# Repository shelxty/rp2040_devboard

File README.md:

# RP2040 Devboard

This is a compact, breakout-friendly devboard (2-layer PCB) built around the Raspberry Pi 2040 microcontroller. It contains an onboard QSPI flash, USB-C, and 30 GPIO pins broken out to dual 20-pin headers. 

It's designed as a base for embedded projects, with every usable GPIO routed to a header pin to be used on a breadboard or custom carrier PCB. 

## Components 

| Reference | Part | Description | Package | 
| ---------- | ----- | ---------- | --------- | 
| U1 | RP2040 | Dual-core MCU | QFN-56, 7x7 mm | 
| U2 | MCPI1700-3.3 | 3.3V LDO regulator | SOT-89-3 | 
| U3 | W25Q128JVS | 16 MB QSPI flash | USON-3, 3x2 mm | 
| Y1 | Crystal | 12 MHz (GND24 style) | 3.2x2.5 mm SMD | 
| J1 | USB-C receptacle | USB 2.0, 14-pin | SMD | 
| J2 | Pin header | GPIO breakout, 1x20 | 2.54 mm THT | 
| SW1 | Tactile switch | BOOTSEL button | SMD | 
| R1, R2 | 5.1kΩ | USB-C CC1/CC2 pull-downs | 0402 |
| R3, R4 | 27Ω | USB D+/D- series termination | 0402 | 
| R5, R7 | 1kΩ | Damping resistors | 0402 |
| R6 | 10kΩ | Standard resistor value from datasheet | 0402 | 
| C1 - C8, C10, C11, C17 | 0.1µF | Decoupling capacitors | 0402 | 
| C9, C12 | 1µF | Decoupling/bulk capacitors | 0402 | 
| C13, C14 | 10µF | Bulk/regulator capacitors | 0603 | 
| C15, C16 | 33pF | Crystal load capacitors | 0201 |

## Flashing and Debugging 

Connect a SWD debug probe to the header J4. 
| J4 Pin | Signal | 
| ------ | ------- |
| 1 | SWCLK | 
| 2 | SWD (SWDIO) | 
| 3 | GND | 

### Powering the Board

Power is supplied over a USB-C (VBUS, 5V) regulated down to 3.3V by U2. No external supply is required for typical use. 

## Design Files

_Kinda messy schematic view_

_Really messy view of PCB design_

_uhhh view of the PCB 3D viewer_

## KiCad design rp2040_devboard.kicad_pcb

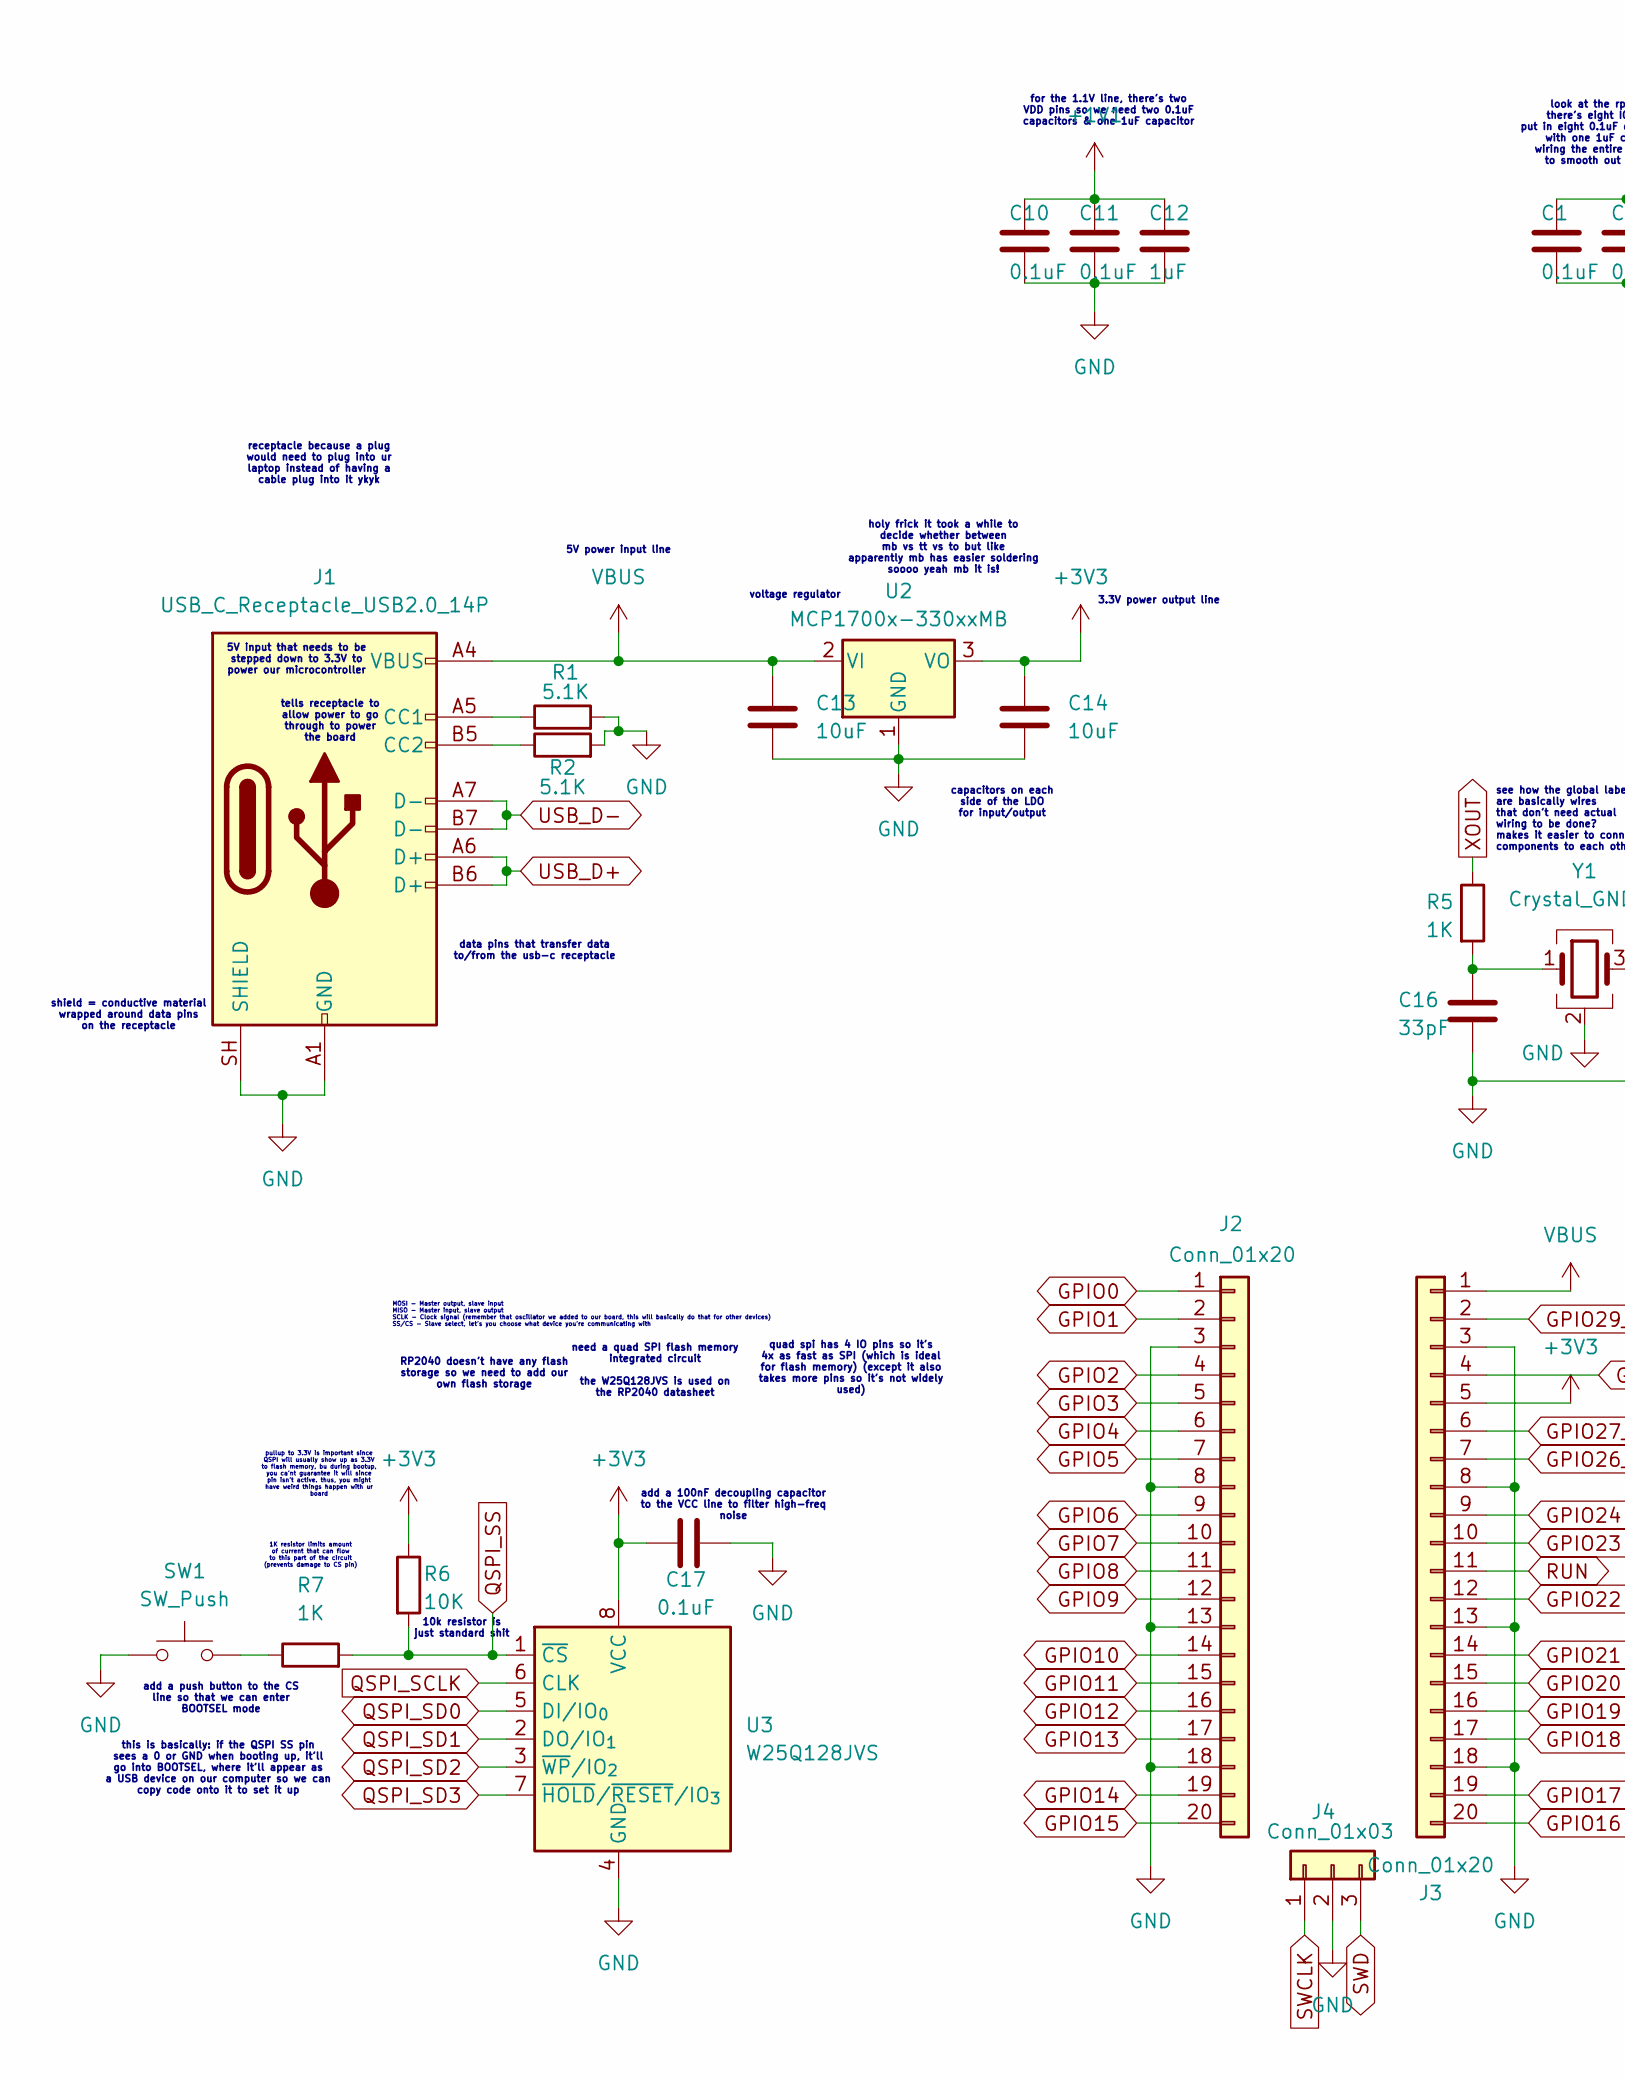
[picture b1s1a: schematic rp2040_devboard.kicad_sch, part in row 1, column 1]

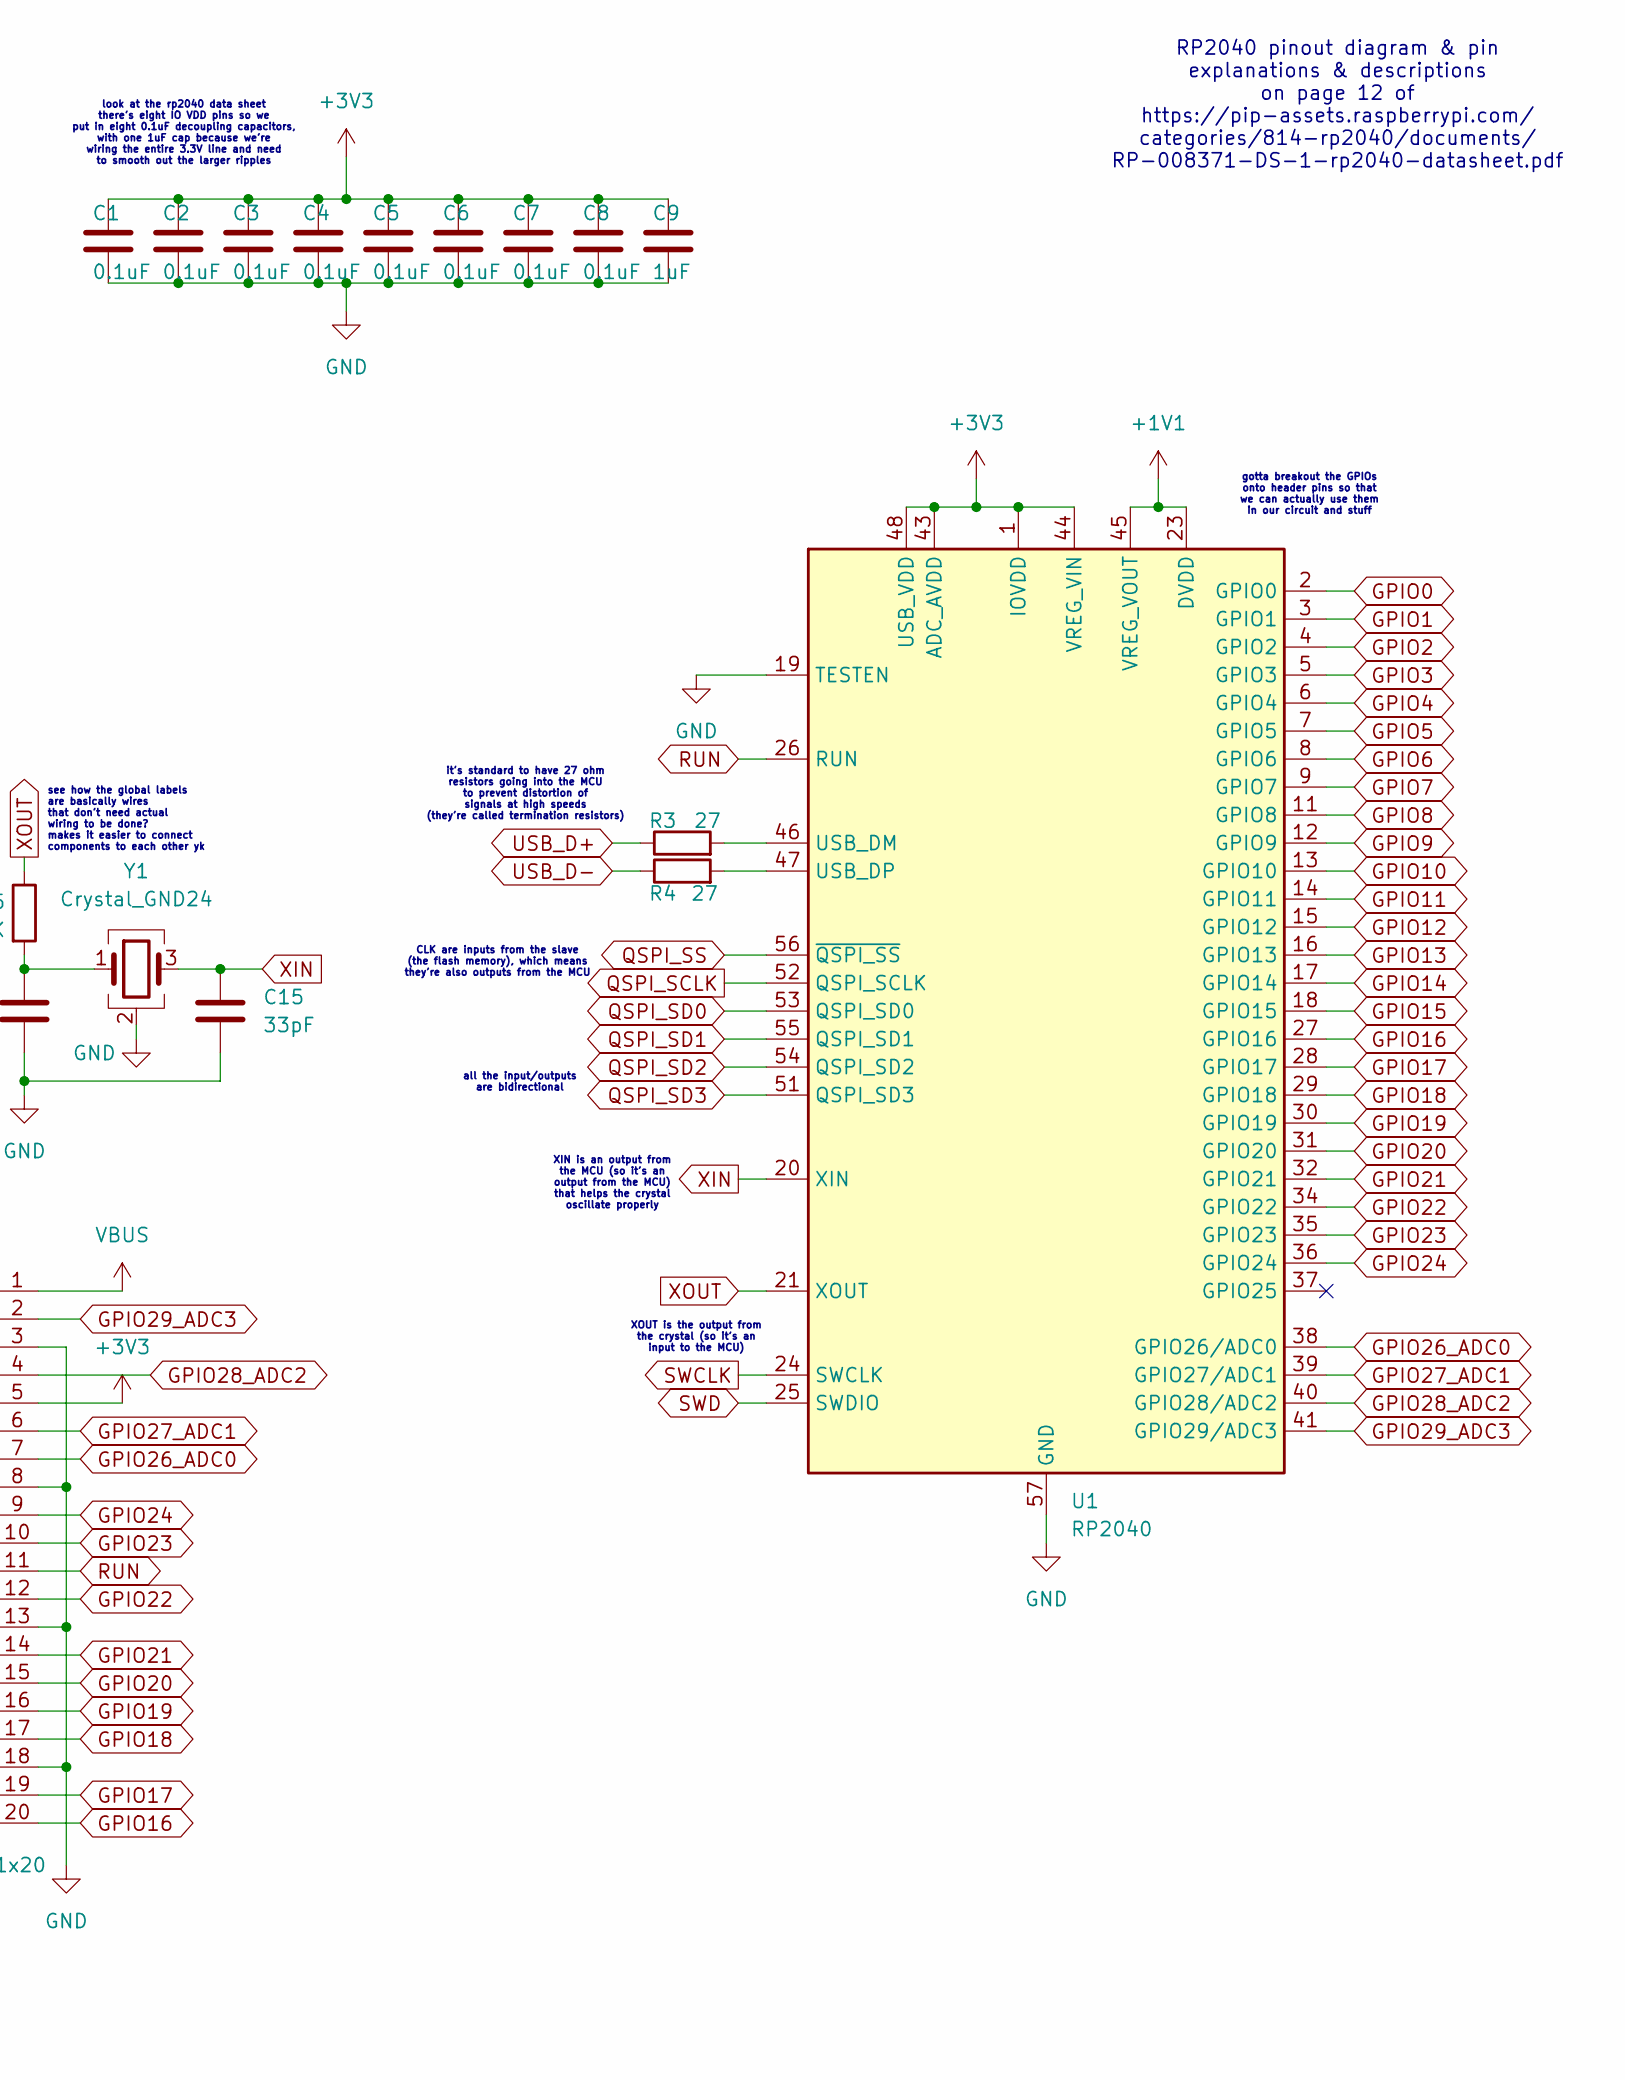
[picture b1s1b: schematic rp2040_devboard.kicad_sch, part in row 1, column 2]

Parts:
C1, C2, C3, C4, C5, C6, C7, C8, C10, C11, C17: 0.1uF; C_0402_1005Metric
C9, C12: 1uF; C_0402_1005Metric
C13, C14: 10uF; C_0201_0603Metric
C15, C16: 33pF; C_0201_0603Metric
J1: USB_C_Receptacle_USB2.0_14P; USB_C_Receptacle_HRO_TYPE-C-31-M-12
J2, J3: Conn_01x20; PinHeader_1x20_P2.54mm_Vertical
J4: Conn_01x03; PinHeader_1x03_P2.54mm_Vertical
R1, R2: 5.1K; R_0402_1005Metric
R3, R4: 27; R_0402_1005Metric
R5, R7: 1K; R_0402_1005Metric
R6: 10K; R_0402_1005Metric
SW1: SW_Push; SW_Push_SPST_NO_Alps_SKRK
U1: RP2040; QFN-56-1EP_7x7mm_P0.4mm_EP3.2x3.2mm
U2: MCP1700x-330xxMB; SOT-89-3
U3: W25Q128JVS; Winbond_USON-8-1EP_3x2mm_P0.5mm_EP0.2x1.6mm
Y1: Crystal_GND24; Crystal_SMD_3225-4Pin_3.2x2.5mm

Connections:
+1V1: C10.1, C11.1, C12.1, U1.23 (DVDD), U1.45 (VREG_VOUT), U1.50 (DVDD)
+3V3: C1.1, C2.1, C3.1, C4.1, C5.1, C6.1, C7.1, C8.1, C9.1, C14.1, C17.1, J3.5, R6.1, U1.1 (IOVDD), U1.10 (IOVDD), U1.22 (IOVDD), U1.33 (IOVDD), U1.42 (IOVDD), U1.43 (ADC_AVDD), U1.44 (VREG_VIN), U1.48 (USB_VDD), U1.49 (IOVDD), U2.3 (VO), U3.8 (VCC)
GND: C1.2, C2.2, C3.2, C4.2, C5.2, C6.2, C7.2, C8.2, C9.2, C10.2, C11.2, C12.2, C13.2, C14.2, C15.1, C16.2, C17.2, J1.A1 (GND), J1.A12 (GND), J1.B1 (GND), J1.B12 (GND), J1.SH (SHIELD), J2.3, J2.8, J2.13, J2.18, J3.3, J3.8, J3.13, J3.18, J4.2, R1.2, R2.2, SW1.1, U1.19 (TESTEN), U1.57 (GND), U2.1 (GND), U3.4 (GND), Y1.2 (G), Y1.4 (G)
GPIO0: J2.1, U1.2 (GPIO0)
GPIO1: J2.2, U1.3 (GPIO1)
GPIO2: J2.4, U1.4 (GPIO2)
GPIO3: J2.5, U1.5 (GPIO3)
GPIO4: J2.6, U1.6 (GPIO4)
GPIO5: J2.7, U1.7 (GPIO5)
GPIO6: J2.9, U1.8 (GPIO6)
GPIO7: J2.10, U1.9 (GPIO7)
GPIO8: J2.11, U1.11 (GPIO8)
GPIO9: J2.12, U1.12 (GPIO9)
GPIO10: J2.14, U1.13 (GPIO10)
GPIO11: J2.15, U1.14 (GPIO11)
GPIO12: J2.16, U1.15 (GPIO12)
GPIO13: J2.17, U1.16 (GPIO13)
GPIO14: J2.19, U1.17 (GPIO14)
GPIO15: J2.20, U1.18 (GPIO15)
GPIO16: J3.20, U1.27 (GPIO16)
GPIO17: J3.19, U1.28 (GPIO17)
GPIO18: J3.17, U1.29 (GPIO18)
GPIO19: J3.16, U1.30 (GPIO19)
GPIO20: J3.15, U1.31 (GPIO20)
GPIO21: J3.14, U1.32 (GPIO21)
GPIO22: J3.12, U1.34 (GPIO22)
GPIO23: J3.10, U1.35 (GPIO23)
GPIO24: J3.9, U1.36 (GPIO24)
GPIO26_ADC0: J3.7, U1.38 (GPIO26/ADC0)
GPIO27_ADC1: J3.6, U1.39 (GPIO27/ADC1)
GPIO28_ADC2: J3.4, U1.40 (GPIO28/ADC2)
GPIO29_ADC3: J3.2, U1.41 (GPIO29/ADC3)
unnamed: C16.1, R5.2, Y1.1
unnamed: J1.A5 (CC1), R1.1
unnamed: J1.B5 (CC2), R2.1
unnamed: R7.1, SW1.2
unnamed: R3.2, U1.46 (USB_DM)
unnamed: R4.2, U1.47 (USB_DP)
QSPI_SCLK: U1.52 (QSPI_SCLK), U3.6 (CLK)
QSPI_SD0: U1.53 (QSPI_SD0), U3.5 (DI/IO_{0})
QSPI_SD1: U1.55 (QSPI_SD1), U3.2 (DO/IO_{1})
QSPI_SD2: U1.54 (QSPI_SD2), U3.3 (~WP/IO_{2})
QSPI_SD3: U1.51 (QSPI_SD3), U3.7 (~HOLD/~RESET/IO_{3})
QSPI_SS: R6.2, R7.2, U1.56 (~QSPI_SS), U3.1 (~CS)
RUN: J3.11, U1.26 (RUN)
SWCLK: J4.1, U1.24 (SWCLK)
SWD: J4.3, U1.25 (SWDIO)
USB_D+: J1.A6 (D+), J1.B6 (D+), R3.1
USB_D-: J1.A7 (D-), J1.B7 (D-), R4.1
VBUS: C13.1, J1.A4 (VBUS), J1.A9 (VBUS), J1.B4 (VBUS), J1.B9 (VBUS), J3.1, U2.2 (VI)
XIN: C15.2, U1.20 (XIN), Y1.3
XOUT: R5.1, U1.21 (XOUT)

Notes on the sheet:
XOUT is the output from the crystal (so it's an input to the MCU)
tells receptacle to allow power to go through to power the board
look at the rp2040 data sheet there's eight IO VDD pins so we put in eight 0.1uF decoupling capacitors, with one 1uF cap because we're wiring the entire 3.3V line and need to smooth out the larger ripples
all the input/outputs are bidirectional
XIN is an output from the MCU (so it's an output from the MCU) that helps the crystal oscillate properly
capacitors on each side of the LDO for input/output
10k resistor is just standard shit
pullup to 3.3V is important since QSPI will usually show up as 3.3V to flash memory, bu during bootup, you ca'nt guarantee it will since pin isn't active. thus, you might have weird things happen with ur board
5V power input line
MOSI - Master output, slave input MISO - Master input, slave output SCLK - Clock signal (remember that oscillator we added to our board, this will basically do that for other devices) SS/CS - Slave select, let's you choose what device you're communicating with
add a 100nF decoupling capacitor to the VCC line to filter high-freq noise
quad spi has 4 IO pins so it's 4x as fast as SPI (which is ideal for flash memory) (except it also takes more pins so it's not widely used)
RP2040 pinout diagram & pin explanations & descriptions on page 12 of https://pip-assets.raspberrypi.com/ categories/814-rp2040/documents/ RP-008371-DS-1-rp2040-datasheet.pdf
this is basically: if the QSPI SS pin sees a 0 or GND when booting up, it'll go into BOOTSEL, where it'll appear as a USB device on our computer so we can copy code onto it to set it up
receptacle because a plug would need to plug into ur laptop instead of having a cable plug into it ykyk
1K resistor limits amount of current that can flow to this part of the circuit (prevents damage to CS pin)
add a push button to the CS line so that we can enter BOOTSEL mode
CLK are inputs from the slave (the flash memory), which means they're also outputs from the MCU
3.3V power output line
shield = conductive material wrapped around data pins on the receptacle
gotta breakout the GPIOs onto header pins so that we can actually use them in our circuit and stuff
need a quad SPI flash memory integrated circuit the W25Q128JVS is used on the RP2040 datasheet
RP2040 doesn't have any flash storage so we need to add our own flash storage
data pins that transfer data to/from the usb-c receptacle
5V input that needs to be stepped down to 3.3V to power our microcontroller
voltage regulator
holy frick it took a while to decide whether between mb vs tt vs to but like apparently mb has easier soldering soooo yeah mb it is!
for the 1.1V line, there's two VDD pins so we need two 0.1uF capacitors & one 1uF capacitor
see how the global labels are basically wires that don't need actual wiring to be done? makes it easier to connect components to each other yk
it's standard to have 27 ohm resistors going into the MCU to prevent distortion of signals at high speeds (they're called termination resistors)

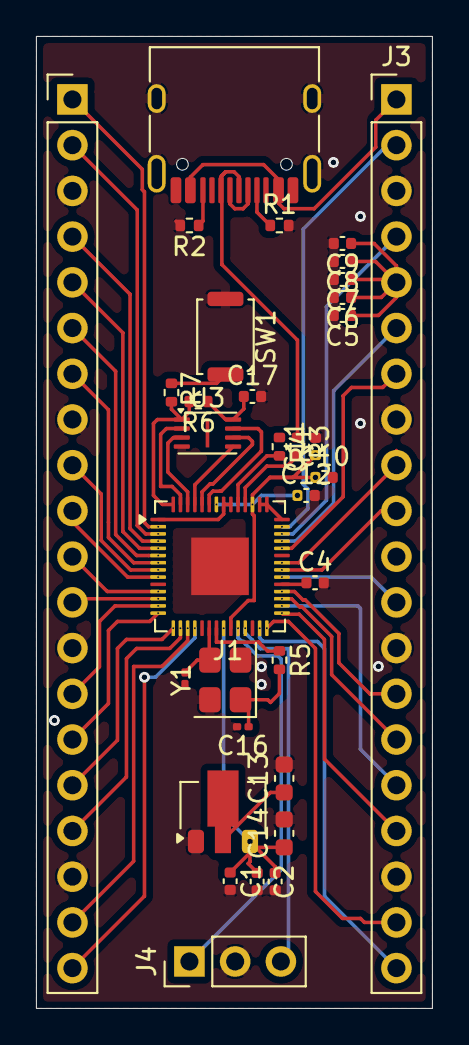
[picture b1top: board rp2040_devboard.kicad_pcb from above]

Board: 2 copper layers, 22.0 x 54.0 mm, 33 parts (0 on the bottom side), 52 nets.
